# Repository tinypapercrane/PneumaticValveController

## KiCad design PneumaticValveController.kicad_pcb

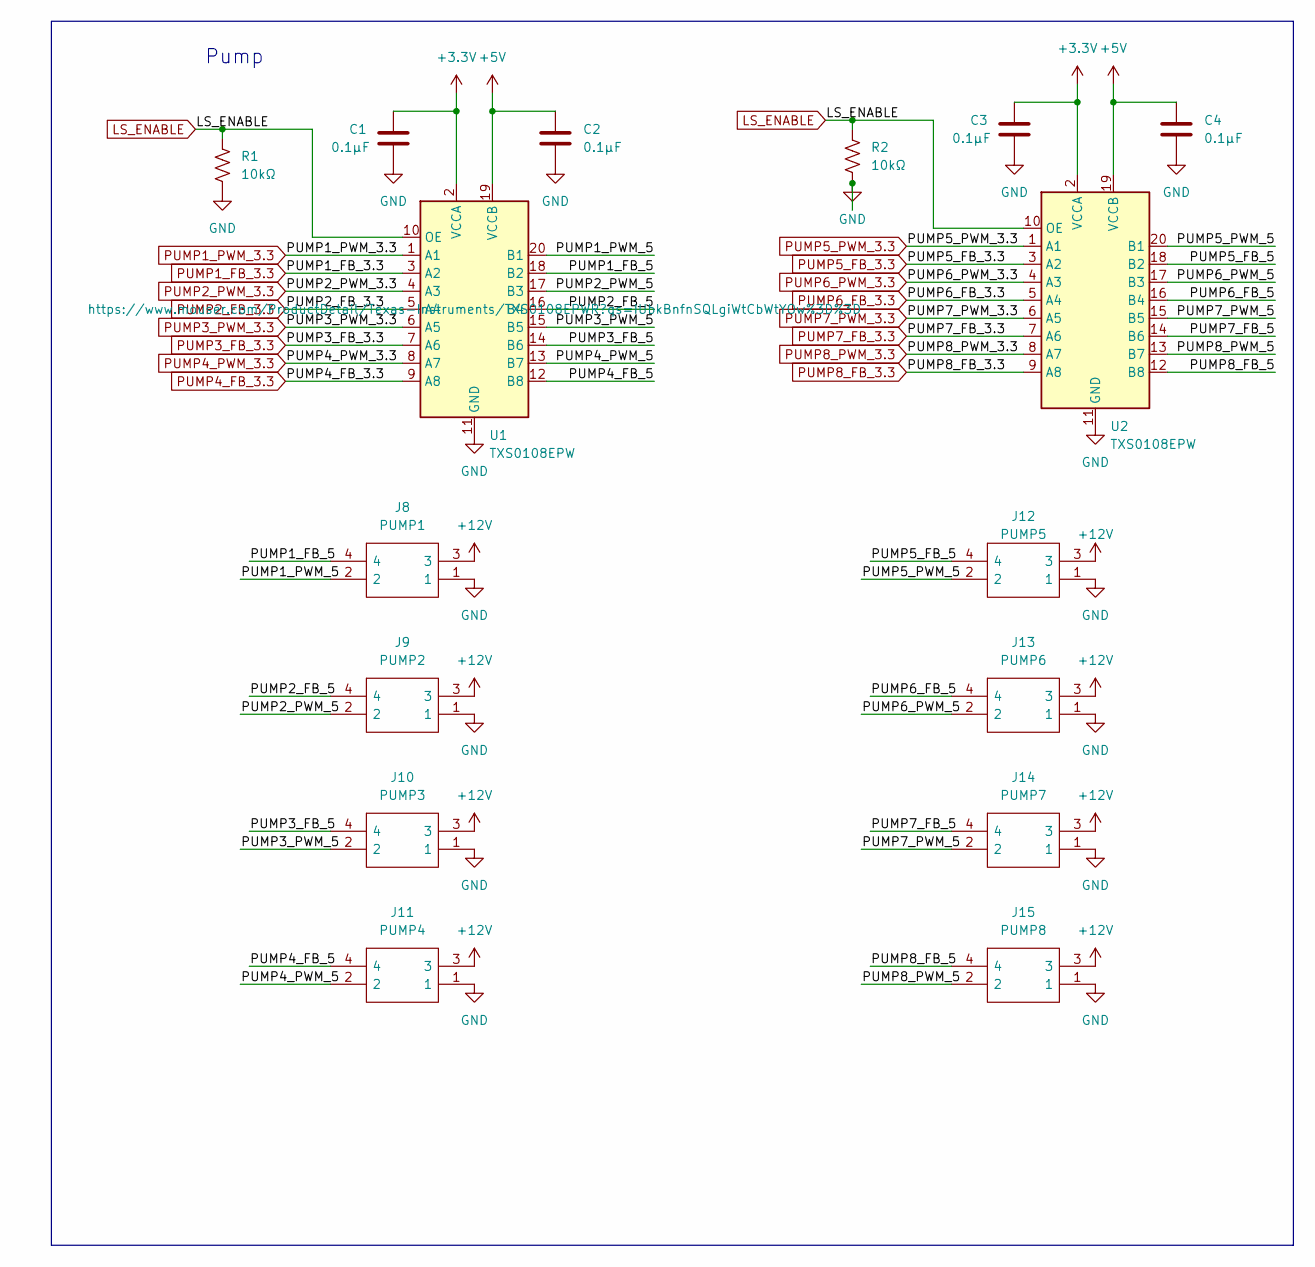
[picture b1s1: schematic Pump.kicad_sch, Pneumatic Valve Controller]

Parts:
C1, C2, C3, C4: 0.1µF; C_0805_2012Metric_Pad1.18x1.45mm_HandSolder
J8: PUMP1; 43045-0412; Mouser Part Number 538-43045-0412
J9: PUMP2; 43045-0412; Mouser Part Number 538-43045-0412
J10: PUMP3; 43045-0412; Mouser Part Number 538-43045-0412
J11: PUMP4; 43045-0412; Mouser Part Number 538-43045-0412
J12: PUMP5; 43045-0412; Mouser Part Number 538-43045-0412
J13: PUMP6; 43045-0412; Mouser Part Number 538-43045-0412
J14: PUMP7; 43045-0412; Mouser Part Number 538-43045-0412
J15: PUMP8; 43045-0412; Mouser Part Number 538-43045-0412
R1, R2: 10kΩ; R_0805_2012Metric_Pad1.20x1.40mm_HandSolder
U1, U2: TXS0108EPW; TSSOP-20_4.4x6.5mm_P0.65mm

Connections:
+3.3V: C1.1, C3.1, U1.2 (VCCA), U2.2 (VCCA); also elsewhere on the board
+5V: C2.1, C4.1, U1.19 (VCCB), U2.19 (VCCB); also elsewhere on the board
+12V: J8.3, J9.3, J10.3, J11.3, J12.3, J13.3, J14.3, J15.3; also elsewhere on the board
/Pump/PUMP1_FB_5: J8.4, U1.18 (B2)
/Pump/PUMP1_PWM_5: J8.2, U1.20 (B1)
/Pump/PUMP2_FB_5: J9.4, U1.16 (B4)
/Pump/PUMP2_PWM_5: J9.2, U1.17 (B3)
/Pump/PUMP3_FB_5: J10.4, U1.14 (B6)
/Pump/PUMP3_PWM_5: J10.2, U1.15 (B5)
/Pump/PUMP4_FB_5: J11.4, U1.12 (B8)
/Pump/PUMP4_PWM_5: J11.2, U1.13 (B7)
/Pump/PUMP5_FB_5: J12.4, U2.18 (B2)
/Pump/PUMP5_PWM_5: J12.2, U2.20 (B1)
/Pump/PUMP6_FB_5: J13.4, U2.16 (B4)
/Pump/PUMP6_PWM_5: J13.2, U2.17 (B3)
/Pump/PUMP7_FB_5: J14.4, U2.14 (B6)
/Pump/PUMP7_PWM_5: J14.2, U2.15 (B5)
/Pump/PUMP8_FB_5: J15.4, U2.12 (B8)
/Pump/PUMP8_PWM_5: J15.2, U2.13 (B7)
GND: C1.2, C2.2, C3.2, C4.2, J8.1, J9.1, J10.1, J11.1, J12.1, J13.1, J14.1, J15.1, R1.2, R2.2, U1.11 (GND), U2.11 (GND); also elsewhere on the board
LS_ENABLE: R1.1, R2.1, U1.10 (OE), U2.10 (OE); also elsewhere on the board
PUMP1_FB_3.3: U1.3 (A2); also elsewhere on the board
PUMP1_PWM_3.3: U1.1 (A1); also elsewhere on the board
PUMP2_FB_3.3: U1.5 (A4); also elsewhere on the board
PUMP2_PWM_3.3: U1.4 (A3); also elsewhere on the board
PUMP3_FB_3.3: U1.7 (A6); also elsewhere on the board
PUMP3_PWM_3.3: U1.6 (A5); also elsewhere on the board
PUMP4_FB_3.3: U1.9 (A8); also elsewhere on the board
PUMP4_PWM_3.3: U1.8 (A7); also elsewhere on the board
PUMP5_FB_3.3: U2.3 (A2); also elsewhere on the board
PUMP5_PWM_3.3: U2.1 (A1); also elsewhere on the board
PUMP6_FB_3.3: U2.5 (A4); also elsewhere on the board
PUMP6_PWM_3.3: U2.4 (A3); also elsewhere on the board
PUMP7_FB_3.3: U2.7 (A6); also elsewhere on the board
PUMP7_PWM_3.3: U2.6 (A5); also elsewhere on the board
PUMP8_FB_3.3: U2.9 (A8); also elsewhere on the board
PUMP8_PWM_3.3: U2.8 (A7); also elsewhere on the board

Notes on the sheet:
Pump

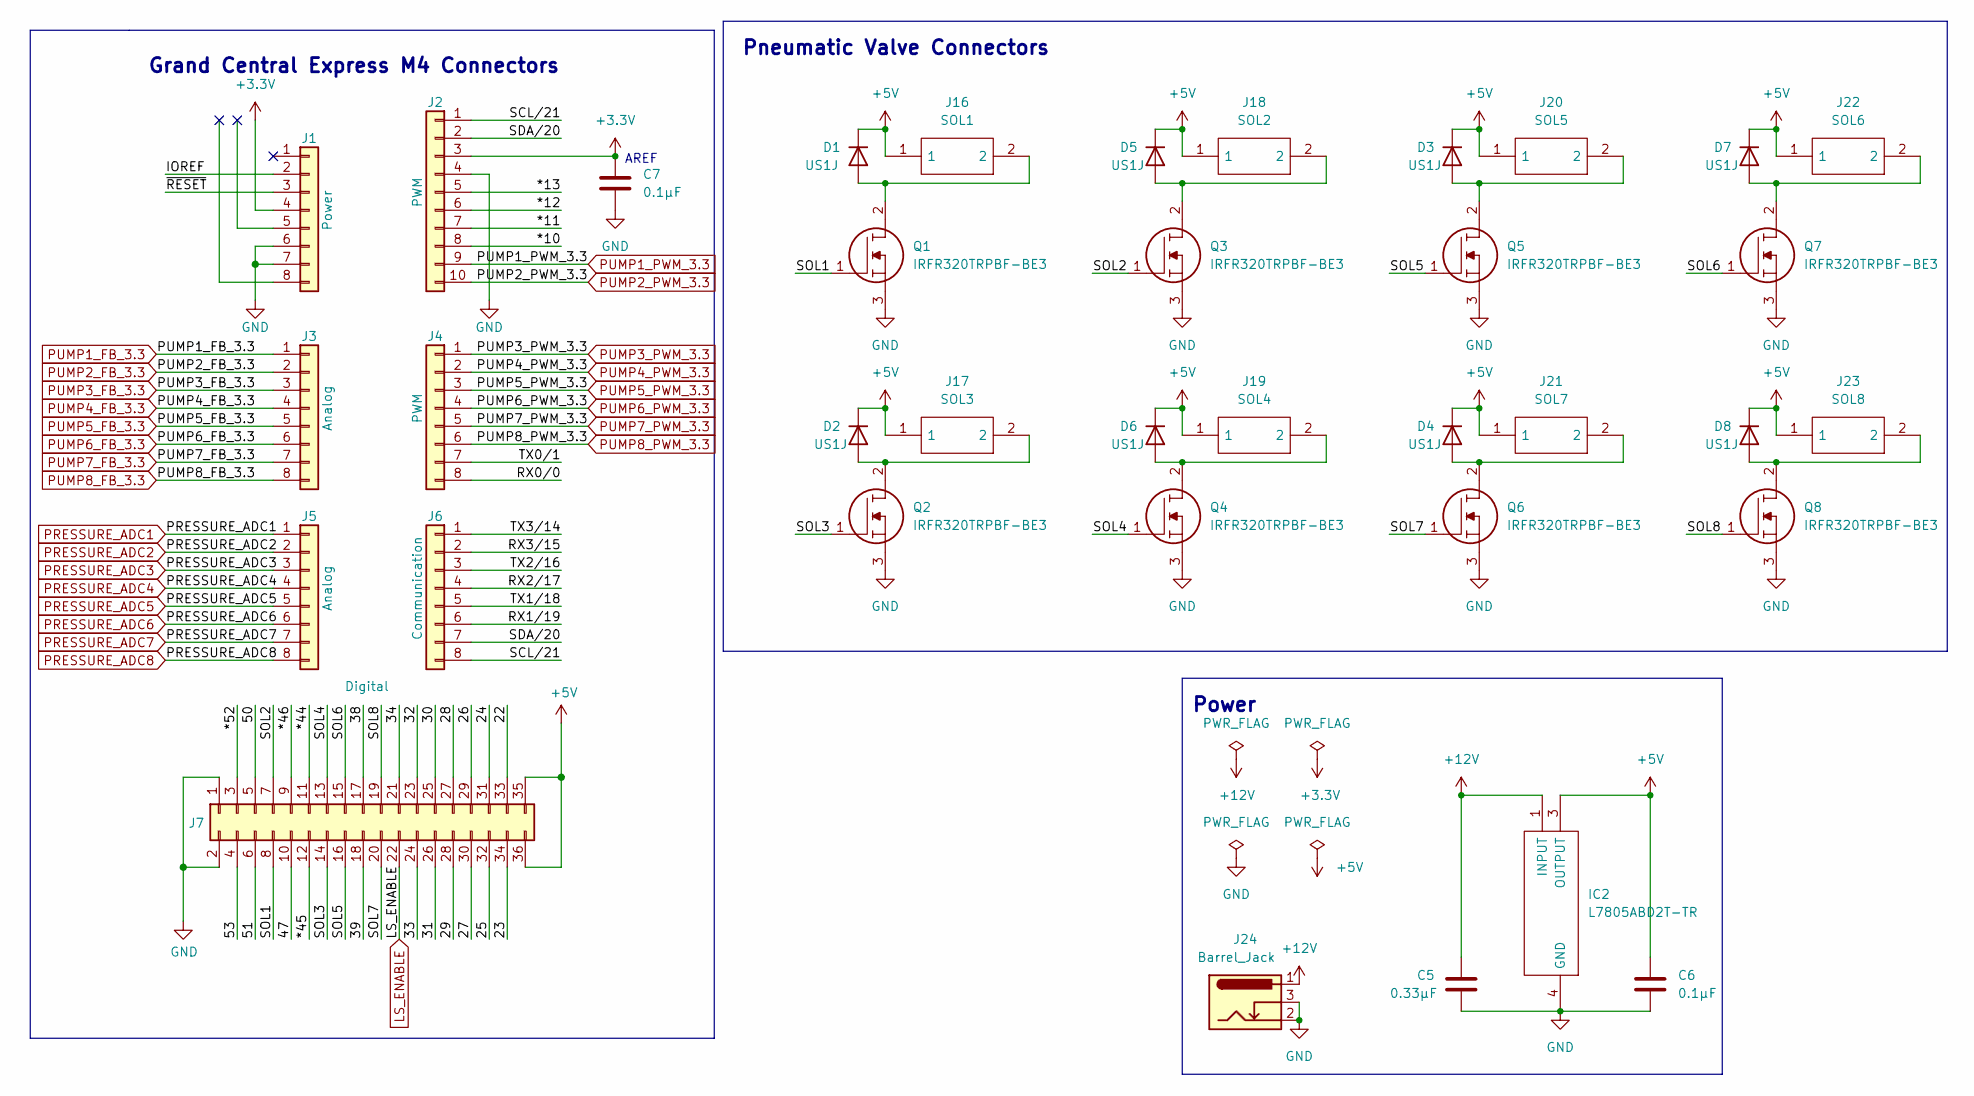
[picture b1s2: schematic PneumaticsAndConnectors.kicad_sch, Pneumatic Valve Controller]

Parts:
C5: 0.33µF; C_0805_2012Metric_Pad1.18x1.45mm_HandSolder
C6, C7: 0.1µF; C_0805_2012Metric_Pad1.18x1.45mm_HandSolder
D1, D2, D3, D4, D5, D6, D7, D8: US1J; D_SMA
IC2: L7805ABD2T-TR; D2PAK-STB35NF10T4; Mouser Part Number 511-L7805ABD2T-TR
J1: Power; PinSocket_1x08_P2.54mm_Vertical
J2: PWM; PinSocket_1x10_P2.54mm_Vertical
J3, J5: Analog; PinSocket_1x08_P2.54mm_Vertical
J4: PWM; PinSocket_1x08_P2.54mm_Vertical
J6: Communication; PinSocket_1x08_P2.54mm_Vertical
J7: Digital; PinSocket_2x18_P2.54mm_Vertical
J16: SOL1; 1990009; Mouser Part Number 651-1990009
J17: SOL3; 1990009; Mouser Part Number 651-1990009
J18: SOL2; 1990009; Mouser Part Number 651-1990009
J19: SOL4; 1990009; Mouser Part Number 651-1990009
J20: SOL5; 1990009; Mouser Part Number 651-1990009
J21: SOL7; 1990009; Mouser Part Number 651-1990009
J22: SOL6; 1990009; Mouser Part Number 651-1990009
J23: SOL8; 1990009; Mouser Part Number 651-1990009
J24: Barrel_Jack; BarrelJack_GCT_DCJ200-10-A_Horizontal
Q1, Q2, Q3, Q4, Q5, Q6, Q7, Q8: IRFR320TRPBF-BE3; IRFR320TRPBFBE3; Mouser Part Number 78-IRFR320TRPBF-BE3

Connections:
+3.3V: C7.1, J1.4, J2.3; also elsewhere on the board
+5V: C6.1, D1.1 (K), D2.1 (K), D3.1 (K), D4.1 (K), D5.1 (K), D6.1 (K), D7.1 (K), D8.1 (K), IC2.3 (OUTPUT), J7.35, J7.36, J16.1, J17.1, J18.1, J19.1, J20.1, J21.1, J22.1, J23.1; also elsewhere on the board
+12V: C5.1, IC2.1 (INPUT), J24.1; also elsewhere on the board
/PneumaticsAndConnectors/22: J7.33
/PneumaticsAndConnectors/23: J7.34
/PneumaticsAndConnectors/24: J7.31
/PneumaticsAndConnectors/25: J7.32
/PneumaticsAndConnectors/26: J7.29
/PneumaticsAndConnectors/27: J7.30
/PneumaticsAndConnectors/28: J7.27
/PneumaticsAndConnectors/29: J7.28
/PneumaticsAndConnectors/30: J7.25
/PneumaticsAndConnectors/31: J7.26
/PneumaticsAndConnectors/32: J7.23
/PneumaticsAndConnectors/33: J7.24
/PneumaticsAndConnectors/34: J7.21
/PneumaticsAndConnectors/38: J7.17
/PneumaticsAndConnectors/39: J7.18
/PneumaticsAndConnectors/47: J7.10
/PneumaticsAndConnectors/50: J7.5
/PneumaticsAndConnectors/51: J7.6
/PneumaticsAndConnectors/53: J7.4
/PneumaticsAndConnectors/*10: J2.8
/PneumaticsAndConnectors/*11: J2.7
/PneumaticsAndConnectors/*12: J2.6
/PneumaticsAndConnectors/*13: J2.5
/PneumaticsAndConnectors/*44: J7.11
/PneumaticsAndConnectors/*45: J7.12
/PneumaticsAndConnectors/*46: J7.9
/PneumaticsAndConnectors/*52: J7.3
/PneumaticsAndConnectors/IOREF: J1.2
/PneumaticsAndConnectors/RX0/0: J4.8
/PneumaticsAndConnectors/RX1/19: J6.6
/PneumaticsAndConnectors/RX2/17: J6.4
/PneumaticsAndConnectors/RX3/15: J6.2
/PneumaticsAndConnectors/SCL/21: J2.1, J6.8
/PneumaticsAndConnectors/SDA/20: J2.2, J6.7
/PneumaticsAndConnectors/SOL1: J7.8, Q1.1
/PneumaticsAndConnectors/SOL2: J7.7, Q3.1
/PneumaticsAndConnectors/SOL3: J7.14, Q2.1
/PneumaticsAndConnectors/SOL4: J7.13, Q4.1
/PneumaticsAndConnectors/SOL5: J7.16, Q5.1
/PneumaticsAndConnectors/SOL6: J7.15, Q7.1
/PneumaticsAndConnectors/SOL7: J7.20, Q6.1
/PneumaticsAndConnectors/SOL8: J7.19, Q8.1
/PneumaticsAndConnectors/TX0/1: J4.7
/PneumaticsAndConnectors/TX1/18: J6.5
/PneumaticsAndConnectors/TX2/16: J6.3
/PneumaticsAndConnectors/TX3/14: J6.1
/PneumaticsAndConnectors/~RESET: J1.3
GND: C5.2, C6.2, C7.2, IC2.4 (GND), J1.6, J1.7, J2.4, J7.1, J7.2, J24.2, J24.3, Q1.3, Q2.3, Q3.3, Q4.3, Q5.3, Q6.3, Q7.3, Q8.3; also elsewhere on the board
LS_ENABLE: J7.22; also elsewhere on the board
unnamed: D1.2 (A), J16.2, Q1.2
unnamed: D2.2 (A), J17.2, Q2.2
unnamed: D3.2 (A), J20.2, Q5.2
unnamed: D4.2 (A), J21.2, Q6.2
unnamed: D5.2 (A), J18.2, Q3.2
unnamed: D6.2 (A), J19.2, Q4.2
unnamed: D7.2 (A), J22.2, Q7.2
unnamed: D8.2 (A), J23.2, Q8.2
PRESSURE_ADC1: J5.1; also elsewhere on the board
PRESSURE_ADC2: J5.2; also elsewhere on the board
PRESSURE_ADC3: J5.3; also elsewhere on the board
PRESSURE_ADC4: J5.4; also elsewhere on the board
PRESSURE_ADC5: J5.5; also elsewhere on the board
PRESSURE_ADC6: J5.6; also elsewhere on the board
PRESSURE_ADC7: J5.7; also elsewhere on the board
PRESSURE_ADC8: J5.8; also elsewhere on the board
PUMP1_FB_3.3: J3.1; also elsewhere on the board
PUMP1_PWM_3.3: J2.9; also elsewhere on the board
PUMP2_FB_3.3: J3.2; also elsewhere on the board
PUMP2_PWM_3.3: J2.10; also elsewhere on the board
PUMP3_FB_3.3: J3.3; also elsewhere on the board
PUMP3_PWM_3.3: J4.1; also elsewhere on the board
PUMP4_FB_3.3: J3.4; also elsewhere on the board
PUMP4_PWM_3.3: J4.2; also elsewhere on the board
PUMP5_FB_3.3: J3.5; also elsewhere on the board
PUMP5_PWM_3.3: J4.3; also elsewhere on the board
PUMP6_FB_3.3: J3.6; also elsewhere on the board
PUMP6_PWM_3.3: J4.4; also elsewhere on the board
PUMP7_FB_3.3: J3.7; also elsewhere on the board
PUMP7_PWM_3.3: J4.5; also elsewhere on the board
PUMP8_FB_3.3: J3.8; also elsewhere on the board
PUMP8_PWM_3.3: J4.6; also elsewhere on the board

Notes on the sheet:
Power
Grand Central Express M4 Connectors
Pneumatic Valve Connectors
AREF

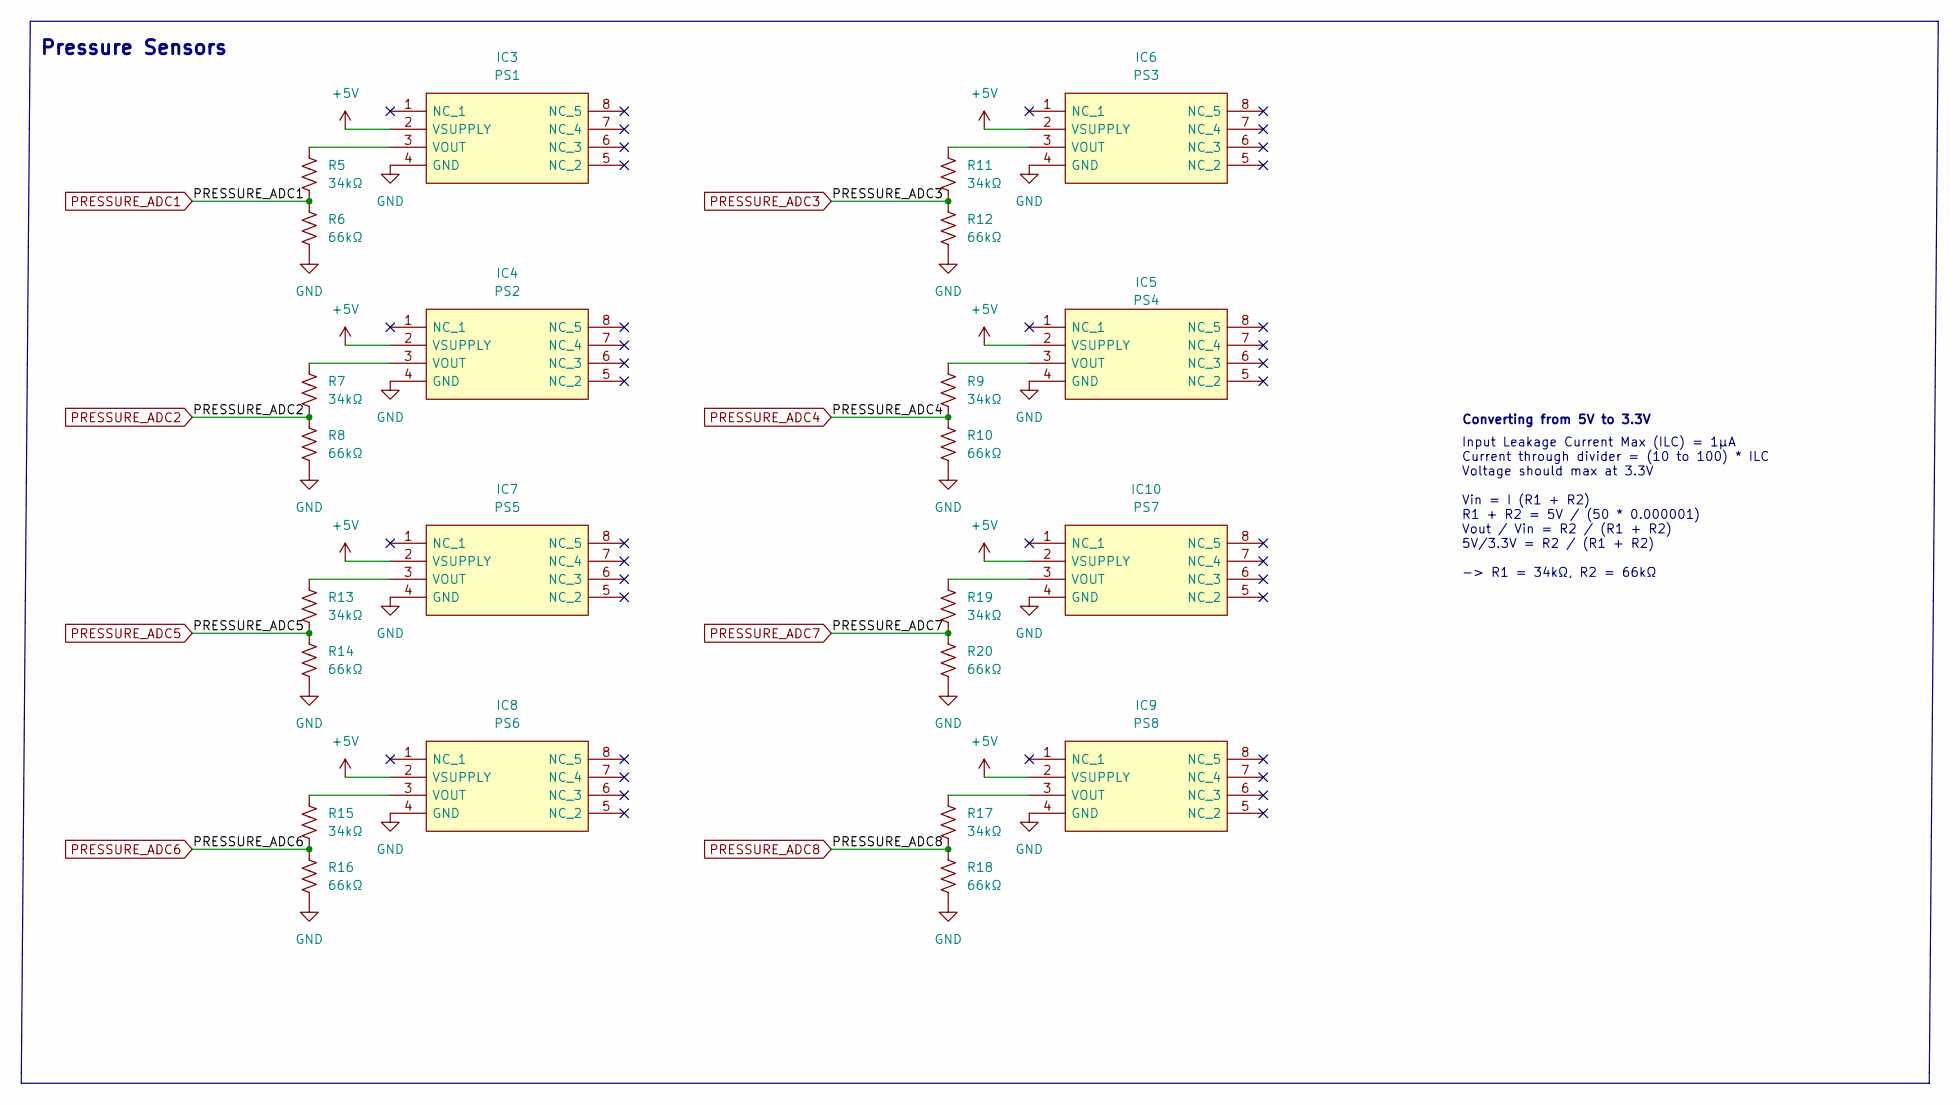
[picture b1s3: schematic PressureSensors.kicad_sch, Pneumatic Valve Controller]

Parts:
IC3: PS1; SSCMANN015PAAA5; Mouser Part Number 785-SSCMANN015PAAA5
IC4: PS2; SSCMANN015PAAA5; Mouser Part Number 785-SSCMANN015PAAA5
IC5: PS4; SSCMANN015PAAA5; Mouser Part Number 785-SSCMANN015PAAA5
IC6: PS3; SSCMANN015PAAA5; Mouser Part Number 785-SSCMANN015PAAA5
IC7: PS5; SSCMANN015PAAA5; Mouser Part Number 785-SSCMANN015PAAA5
IC8: PS6; SSCMANN015PAAA5; Mouser Part Number 785-SSCMANN015PAAA5
IC9: PS8; SSCMANN015PAAA5; Mouser Part Number 785-SSCMANN015PAAA5
IC10: PS7; SSCMANN015PAAA5; Mouser Part Number 785-SSCMANN015PAAA5
R5, R7, R9, R11, R13, R15, R17, R19: 34kΩ; R_0603_1608Metric_Pad0.98x0.95mm_HandSolder
R6, R8, R10, R12, R14, R16, R18, R20: 66kΩ; R_0603_1608Metric_Pad0.98x0.95mm_HandSolder

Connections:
+5V: IC3.2 (VSUPPLY), IC4.2 (VSUPPLY), IC5.2 (VSUPPLY), IC6.2 (VSUPPLY), IC7.2 (VSUPPLY), IC8.2 (VSUPPLY), IC9.2 (VSUPPLY), IC10.2 (VSUPPLY); also elsewhere on the board
GND: IC3.4 (GND), IC4.4 (GND), IC5.4 (GND), IC6.4 (GND), IC7.4 (GND), IC8.4 (GND), IC9.4 (GND), IC10.4 (GND), R6.2, R8.2, R10.2, R12.2, R14.2, R16.2, R18.2, R20.2; also elsewhere on the board
unnamed: IC3.3 (VOUT), R5.1
unnamed: IC4.3 (VOUT), R7.1
unnamed: IC5.3 (VOUT), R9.1
unnamed: IC6.3 (VOUT), R11.1
unnamed: IC7.3 (VOUT), R13.1
unnamed: IC8.3 (VOUT), R15.1
unnamed: IC9.3 (VOUT), R17.1
unnamed: IC10.3 (VOUT), R19.1
PRESSURE_ADC1: R5.2, R6.1; also elsewhere on the board
PRESSURE_ADC2: R7.2, R8.1; also elsewhere on the board
PRESSURE_ADC3: R11.2, R12.1; also elsewhere on the board
PRESSURE_ADC4: R9.2, R10.1; also elsewhere on the board
PRESSURE_ADC5: R13.2, R14.1; also elsewhere on the board
PRESSURE_ADC6: R15.2, R16.1; also elsewhere on the board
PRESSURE_ADC7: R19.2, R20.1; also elsewhere on the board
PRESSURE_ADC8: R17.2, R18.1; also elsewhere on the board

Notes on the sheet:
Converting from 5V to 3.3V
Input Leakage Current Max (ILC) = 1µA Current through divider = (10 to 100) * ILC Voltage should max at 3.3V Vin = I (R1 + R2) R1 + R2 = 5V / (50 * 0.000001) Vout / Vin = R2 / (R1 + R2) 5V/3.3V = R2 / (R1 + R2) -> R1 = 34kΩ, R2 = 66kΩ
Pressure Sensors

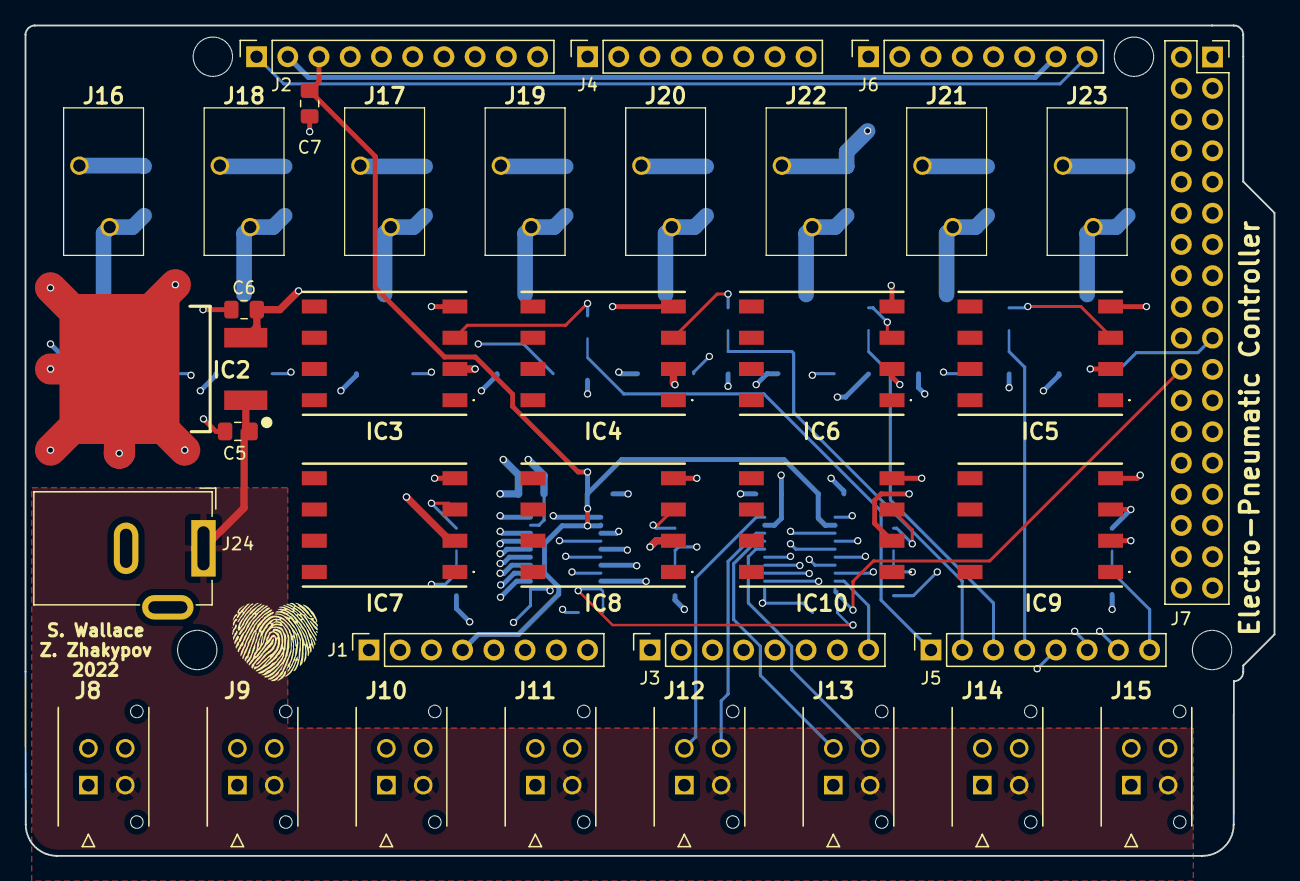
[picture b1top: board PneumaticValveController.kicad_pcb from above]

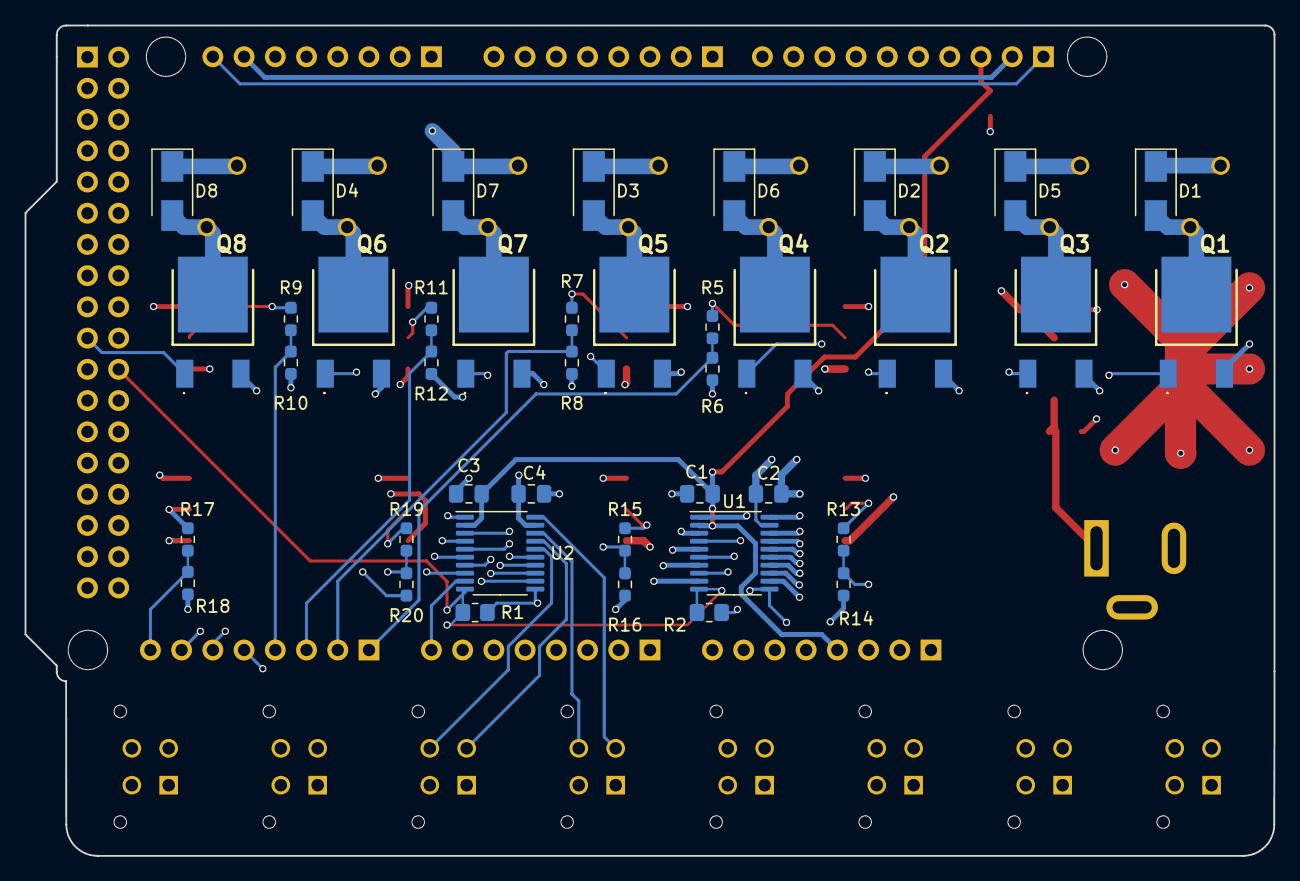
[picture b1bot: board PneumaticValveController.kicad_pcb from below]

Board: 4 copper layers, 101.6 x 67.5 mm, 80 parts (40 on the bottom side), 71 nets.

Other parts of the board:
MH1, MH2, MH5, MH6: MountingHole_3.2mm

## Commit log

2022-11-13 Added files
2022-11-15 Add files via upload
    Chnges 11/15/2022
